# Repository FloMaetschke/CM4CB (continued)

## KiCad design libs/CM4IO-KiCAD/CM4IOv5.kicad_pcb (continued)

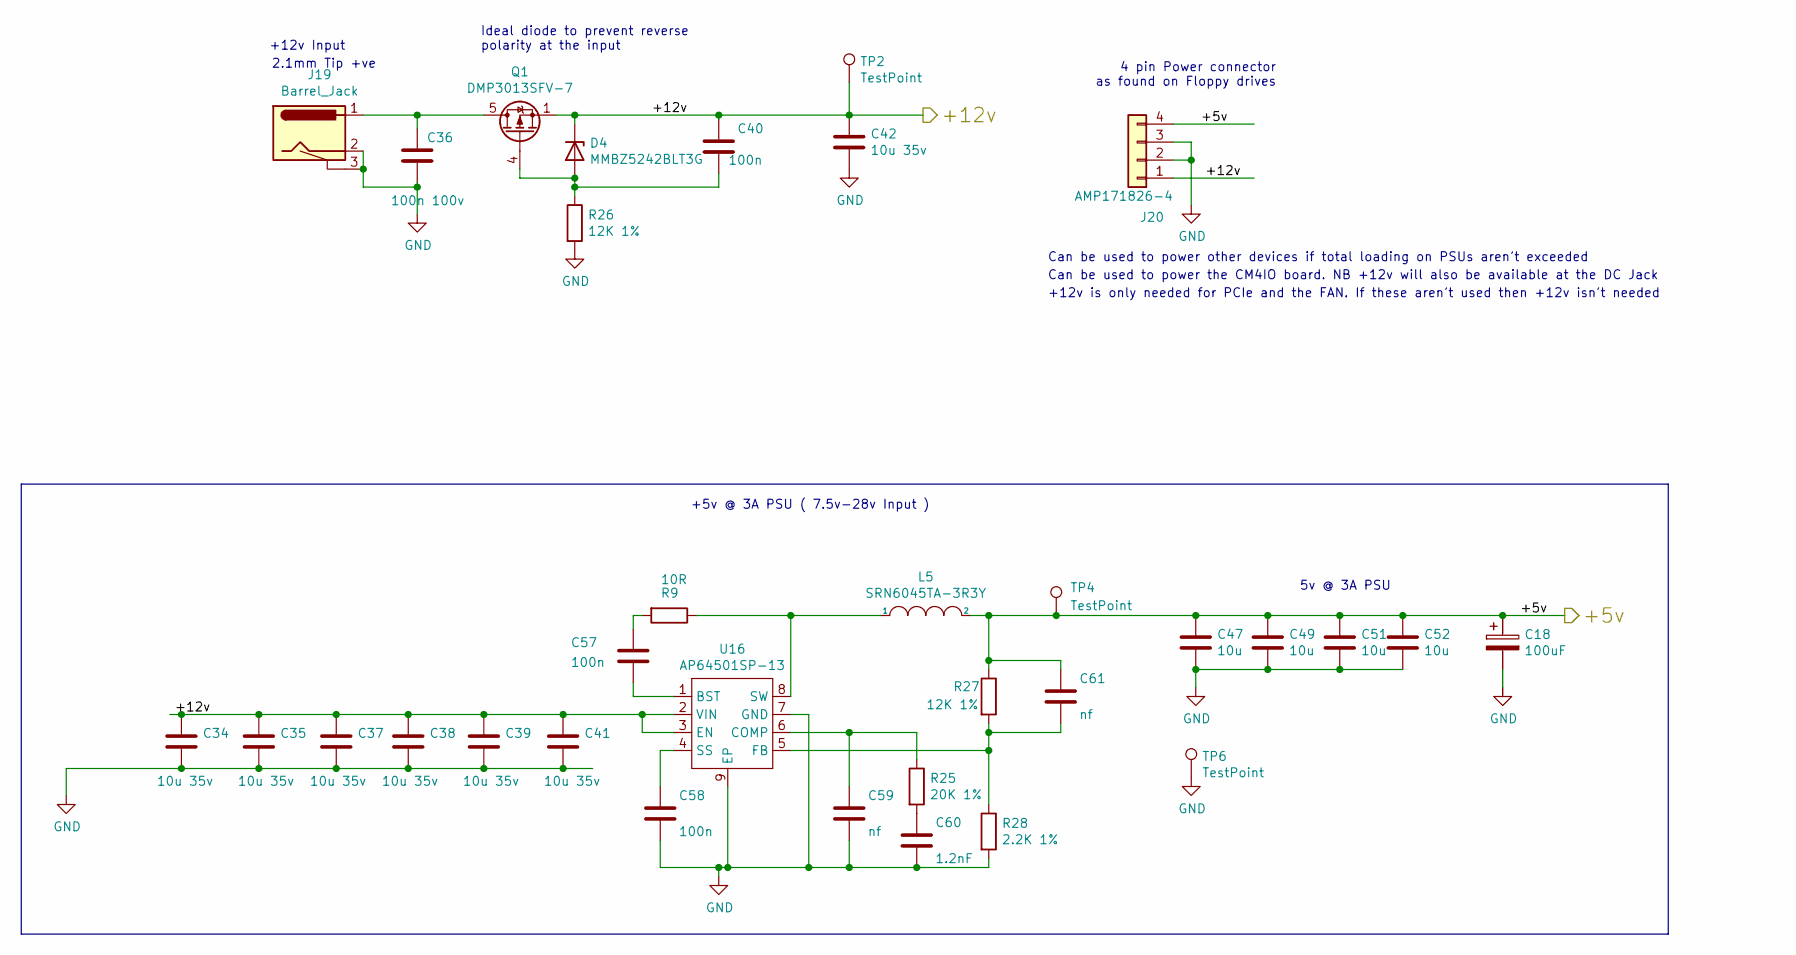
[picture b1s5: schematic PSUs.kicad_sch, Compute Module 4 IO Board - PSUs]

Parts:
C18: 100uF; CP_EIA-7343-31_Kemet-D; Part Description Capacitor, SP-Cap, 100u, 6.3V, 15mR ESR
C34, C35, C37, C38, C39, C41, C42: 10u 35v; C_0805_2012Metric; Part Description 10uF 10% or 20% 35V Ceramic Capacitor X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
C36: 100n 100v; C_0402_1005Metric; Part Description 0.1uF 10% 100V Ceramic Capacitor X5R 04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
C40, C57, C58: 100n; C_0402_1005Metric; Part Description 0.1uF 10% 16V Ceramic Capacitor X7R 040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
C47, C49, C51, C52: 10u; C_0805_2012Metric; Part Description 10uF 10% 10V Ceramic Capacitor X7R 0805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
C59: nf; C_0402_1005Metric
C60: 1.2nF; C_0402_1005Metric; Part Description 1200pF 10% 10V Ceramic Capacitor X5R 04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
C61: nf; C_0402_1005Metric; Part Description 220 pF, 50 V, 0402 [1005 Metric], ± 5%,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
D4: MMBZ5242BLT3G; D_SOT-23_ANK; Part Description Zener Diode 12V 225mW 5% Surface Mount 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
J19: Barrel_Jack; BarrelJack_Horizontal; Part Description DC Power Connectors PCB 2.1MM
J20: AMP171826-4; TE_171826-4; Part Description Wire-To-Board Connector, Right Angle, 2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
L5: SRN6045TA-3R3Y; L_Bourns_SRN6045TA; Part Description 3.3µH Semi-Shielded Wirewound Inductor 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
Q1: DMP3013SFV-7; Diodes_PowerDI3333-8; Part Description DMP3013SFV-7 - Power MOSFET, P Channel,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
R9: 10R; R_0402_1005Metric; Part Description Resistor 10R M1005 1% 63mW
R25: 20K 1%; R_0402_1005Metric; Part Description Resistor 20K M1005 1% 63mW
R26, R27: 12K 1%; R_0402_1005Metric; Part Description Resistor 12K M1005 1% 63mW
R28: 2.2K 1%; R_0402_1005Metric; Part Description Resistor 2.2K M1005 1% 63mW
TP2, TP4, TP6: TestPoint; TestPoint_Pad_2.0x2.0mm
U16: AP64501SP-13; SOIC-8-1EP_3.9x4.9mm_P1.27mm_EP2.95x4.9mm_Mask2.71x3.4mm_Th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; Part Description Buck Switching Regulator IC Positive Ad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

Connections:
/+5v: C18.1, C47.1, C49.1, C51.1, C52.1, C61.1, J20.4, L5.2, R27.1, TP4.1; also elsewhere on the board
/+12v: C34.1, C35.1, C37.1, C38.1, C39.1, C40.1, C41.1, C42.1, D4.1 (K), J20.1, Q1.1 (S), Q1.2 (S), Q1.3 (S), TP2.1, U16.2 (VIN), U16.3 (EN); also elsewhere on the board
GND: C18.2, C34.2, C35.2, C36.2, C37.2, C38.2, C39.2, C41.2, C42.2, C47.2, C49.2, C51.2, C52.2, C58.2, C59.2, C60.2, J19.2, J19.3, J20.2, J20.3, R26.2, R28.2, TP6.1, U16.7 (GND), U16.9 (EP); also elsewhere on the board
unnamed: C36.1, J19.1, Q1.5 (D)
unnamed: C40.2, D4.2 (A), Q1.4 (G), R26.1
unnamed: C57.1, R9.2
unnamed: C57.2, U16.1 (BST)
unnamed: C58.1, U16.4 (SS)
unnamed: C59.1, R25.1, U16.6 (COMP)
unnamed: C60.1, R25.2
unnamed: C61.2, R27.2, R28.1, U16.5 (FB)
unnamed: L5.1, R9.1, U16.8 (SW)

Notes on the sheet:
+12v Input
2.1mm Tip +ve
Ideal diode to prevent reverse polarity at the input
+5v @ 3A PSU ( 7.5v-28v Input )
Can be used to power other devices if total loading on PSUs aren't exceeded
Can be used to power the CM4IO board. NB +12v will also be available at the DC Jack
+12v is only needed for PCIe and the FAN. If these aren't used then +12v isn't needed
4 pin Power connector as found on Floppy drives
5v @ 3A PSU

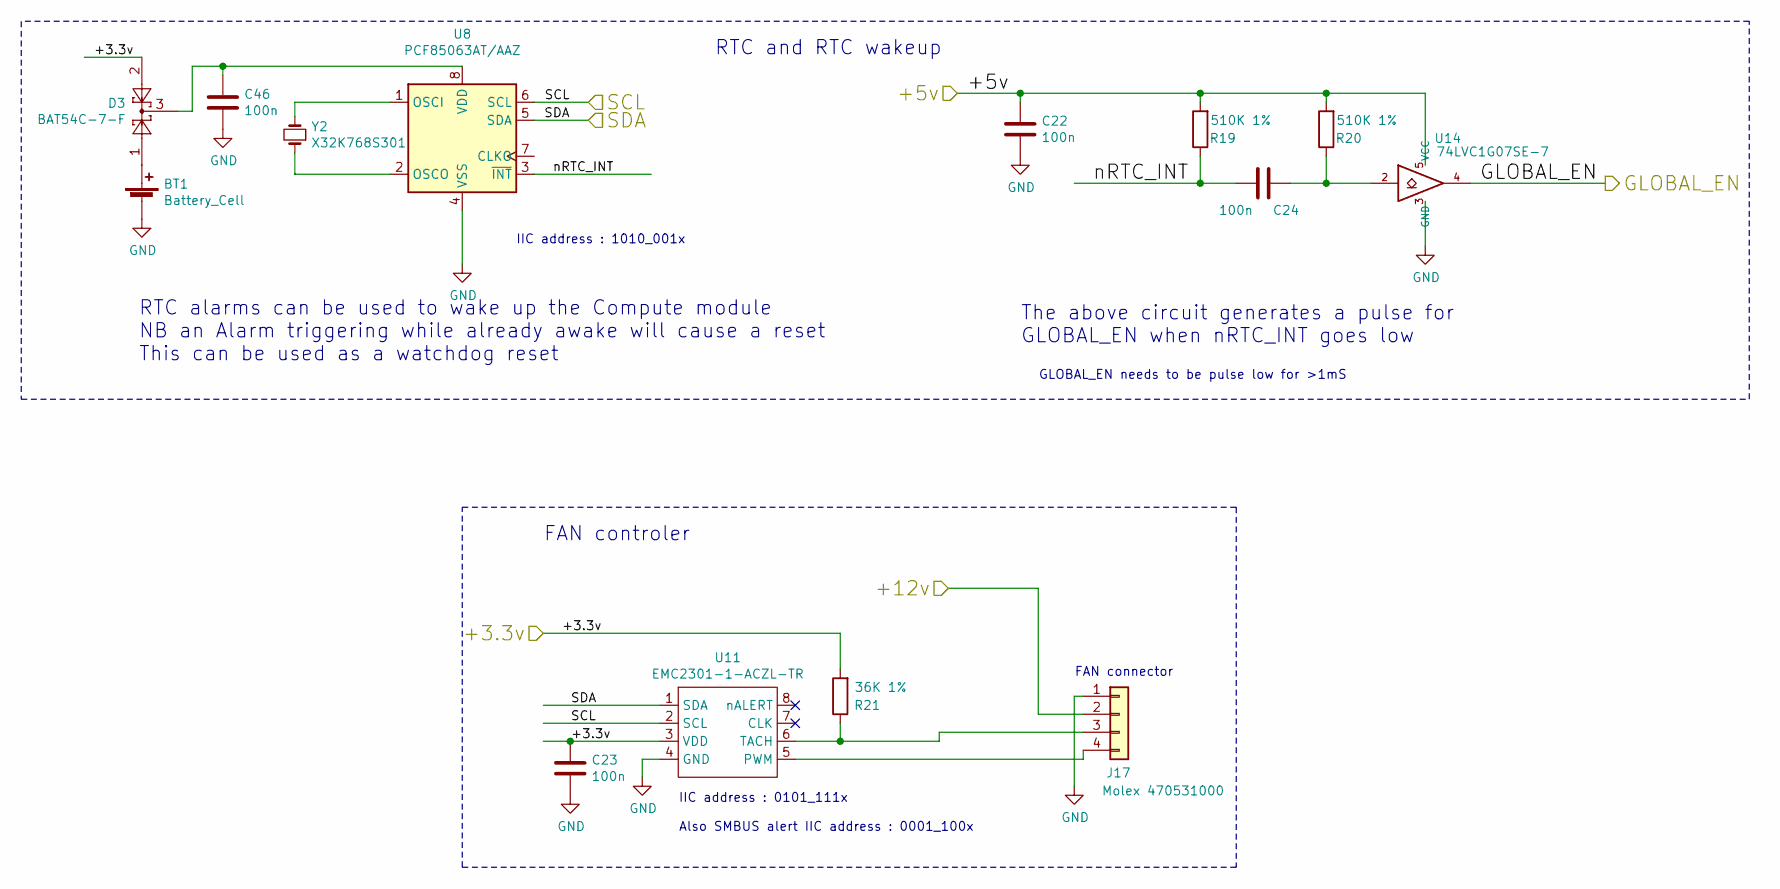
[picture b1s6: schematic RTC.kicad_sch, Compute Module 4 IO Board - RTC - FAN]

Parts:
BT1: Battery_Cell; BatteryHolder_Keystone_3034_1x20mm; Part Description Battery Retainer Coin, 20.0mm 1 Cell SM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
C22, C23, C24, C46: 100n; C_0402_1005Metric; Part Description 0.1uF 10% 16V Ceramic Capacitor X7R 040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
D3: BAT54C-7-F; SOT-23; Part Description Diode Array 1 Pair Common Cathode Schot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
J17: Molex 470531000; FanPinHeader_1x04_P2.54mm_Vertical; Part Description Connector Header Through Hole 4 positio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
R19, R20: 510K 1%; R_0402_1005Metric; Part Description Resistor 510K M1005 1% 63mW
R21: 36K 1%; R_0402_1005Metric; Part Description Resistor 36K M1005 1% 63mW
U8: PCF85063AT/AAZ; SOIC-8_3.9x4.9mm_P1.27mm; Part Description Real Time Clock (RTC) IC Clock/Calendar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
U11: EMC2301-1-ACZL-TR; SOIC-8_5.23x5.23mm_P1.27mm; Part Description Motor Driver PWM 8-MSOP
U14: 74LVC1G07SE-7; SOT-353_SC-70-5; Part Description Buffer, Non-Inverting 1 Element 1 Bit p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
Y2: X32K768S301; Crystal_SMD_3215-2Pin_3.2x1.5mm; Part Description Crystal 32.768KHz 7pF 20pmm

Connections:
/+3.3v: C23.1, D3.2, R21.2, U11.3 (VDD); also elsewhere on the board
/+5v: C22.1, R19.2, R20.2, U14.5 (VCC); also elsewhere on the board
/+12v: J17.2; also elsewhere on the board
/GLOBAL_EN: U14.4; also elsewhere on the board
/RTC , Wakeup, FAN/nRTC_INT: C24.2, R19.1, U8.3 (~INT~)
/SCL0: U8.6 (SCL), U11.2 (SCL); also elsewhere on the board
/SDA0: U8.5 (SDA), U11.1 (SDA); also elsewhere on the board
GND: BT1.2 (-), C22.2, C23.2, C46.2, J17.1, U8.4 (VSS), U11.4 (GND), U14.3 (GND); also elsewhere on the board
unnamed: BT1.1 (+), D3.1
unnamed: C24.1, R20.1, U14.2
unnamed: C46.1, D3.3, U8.8 (VDD)
unnamed: J17.3, R21.1, U11.6 (TACH)
unnamed: J17.4, U11.5 (PWM)
unnamed: U8.1 (OSCI), Y2.2
unnamed: U8.2 (OSCO), Y2.1

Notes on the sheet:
RTC alarms can be used to wake up the Compute module NB an Alarm triggering while already awake will cause a reset This can be used as a watchdog reset
IIC address : 1010_001x
FAN controler
IIC address : 0101_111x
Also SMBUS alert IIC address : 0001_100x
RTC and RTC wakeup
The above circuit generates a pulse for GLOBAL_EN when nRTC_INT goes low
GLOBAL_EN needs to be pulse low for >1mS
FAN connector

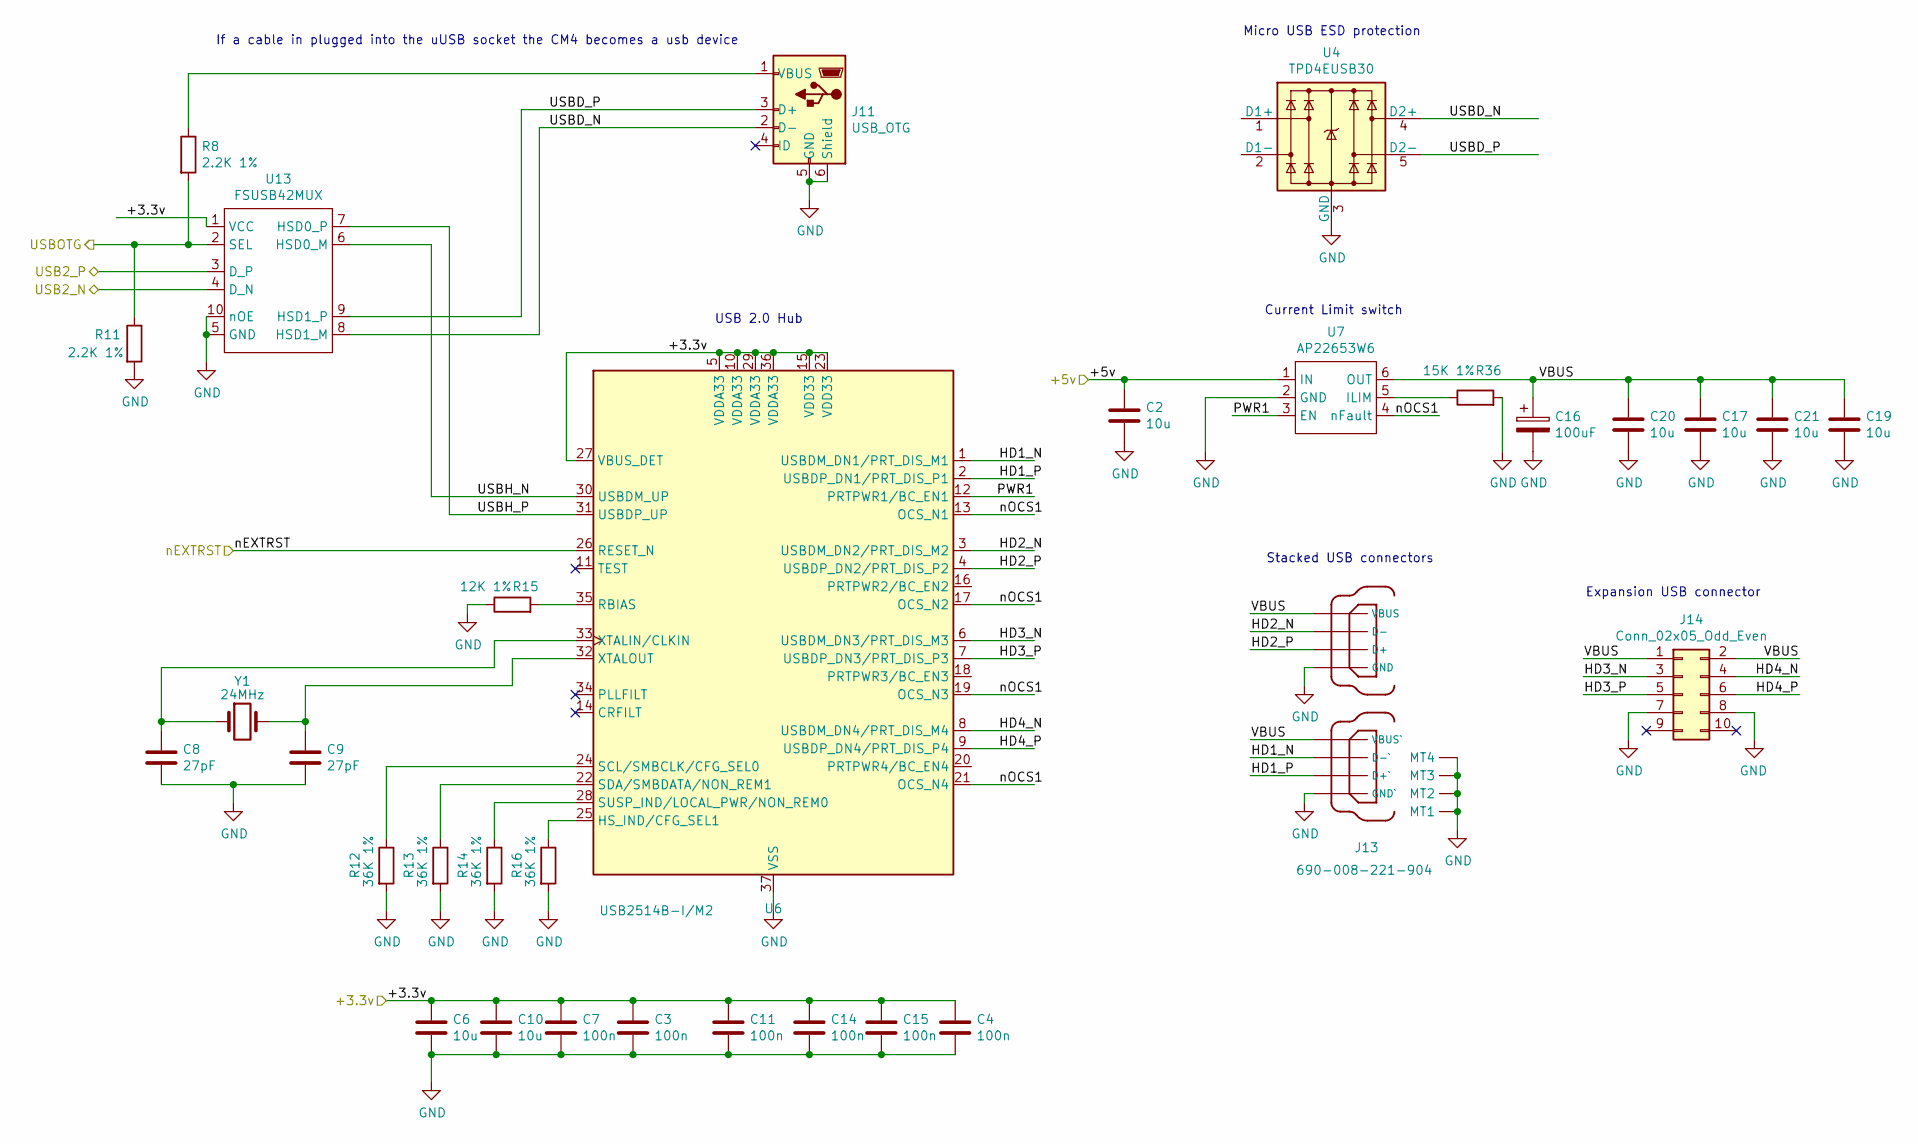
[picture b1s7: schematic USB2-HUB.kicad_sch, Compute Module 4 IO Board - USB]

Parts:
C2, C6, C10, C17, C19, C20, C21: 10u; C_0805_2012Metric; Part Description 10uF 10% 10V Ceramic Capacitor X7R 0805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
C3, C4, C7, C11, C14, C15: 100n; C_0402_1005Metric; Part Description 0.1uF 10% 16V Ceramic Capacitor X7R 040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
C8, C9: 27pF; C_0402_1005Metric; Part Description 27pF 5% 50V Ceramic Capacitor C0G, NP0 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
C16: 100uF; CP_EIA-7343-31_Kemet-D; Part Description Capacitor, SP-Cap, 100u, 6.3V, 15mR ESR
J11: USB_OTG; USB_Micro-B_EDAC_UCON00686; Part Description USB - micro B USB 2.0 Receptacle Connec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
J13: 690-008-221-904; MOLEX_USB_67298-4090; Part Description USB-A (USB TYPE-A), Stacked Receptacle 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
J14: Conn_02x05_Odd_Even; PinHeader_2x05_P2.54mm_Vertical; Part Description PinHeader_2x05_P2.54mm_Vertical
R8, R11: 2.2K 1%; R_0402_1005Metric; Part Description Resistor 2.2K M1005 1% 63mW
R12, R13, R14, R16: 36K 1%; R_0402_1005Metric; Part Description Resistor 36K M1005 1% 63mW
R15: 12K 1%; R_0402_1005Metric; Part Description Resistor 12K M1005 1% 63mW
R36: 15K 1%; R_0402_1005Metric; Part Description Resistor 15K M1005 1% 63mW
U4: TPD4EUSB30; USON-10_2.5x1.0mm_P0.5mm; Part Description Quad TVS diode for high speed signals (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
U6: USB2514B-I/M2; QFN-36-1EP_6x6mm_P0.5mm_EP3.7x3.7mm; Part Description USB Hub Controller USB Interface 36-SQF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
U7: AP22653W6; SOT-23-6; Part Description Power Switch/Driver 1:1 P-Channel 2.1A 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
U13: FSUSB42MUX; MSOP-10_3x3mm_P0.5mm; Part Description USB Switch IC 1 Channel 10-MSOP
Y1: 24MHz; Crystal_SMD_HC49-SD; Part Description 24MHz Crystal 18pf 30ppm 30ppm

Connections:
/+3.3v: C3.1, C4.1, C6.1, C7.1, C10.1, C11.1, C14.1, C15.1, U6.5 (VDDA33), U6.10 (VDDA33), U6.15 (VDD33), U6.23 (VDD33), U6.27 (VBUS_DET), U6.29 (VDDA33), U6.36 (VDDA33), U13.1 (VCC); also elsewhere on the board
/+5v: C2.1, U7.1 (IN); also elsewhere on the board
/USB2-HUB/HD1_N: J13.2 (D-`), U6.1 (USBDM_DN1/PRT_DIS_M1)
/USB2-HUB/HD1_P: J13.3 (D+`), U6.2 (USBDP_DN1/PRT_DIS_P1)
/USB2-HUB/HD2_N: J13.6 (D-), U6.3 (USBDM_DN2/PRT_DIS_M2)
/USB2-HUB/HD2_P: J13.7 (D+), U6.4 (USBDP_DN2/PRT_DIS_P2)
/USB2-HUB/HD3_N: J14.3, U6.6 (USBDM_DN3/PRT_DIS_M3)
/USB2-HUB/HD3_P: J14.5, U6.7 (USBDP_DN3/PRT_DIS_P3)
/USB2-HUB/HD4_N: J14.4, U6.8 (USBDM_DN4/PRT_DIS_M4)
/USB2-HUB/HD4_P: J14.6, U6.9 (USBDP_DN4/PRT_DIS_P4)
/USB2-HUB/PWR1: U6.12 (PRTPWR1/BC_EN1), U7.3 (EN)
/USB2-HUB/USBD_N: J11.2 (D-), U4.4 (D2+), U4.7, U13.8 (HSD1_M)
/USB2-HUB/USBD_P: J11.3 (D+), U4.5 (D2-), U4.6, U13.9 (HSD1_P)
/USB2-HUB/USBH_N: U6.30 (USBDM_UP), U13.6 (HSD0_M)
/USB2-HUB/USBH_P: U6.31 (USBDP_UP), U13.7 (HSD0_P)
/USB2-HUB/VBUS: C16.1, C17.1, C19.1, C20.1, C21.1, J13.1 (VBUS`), J13.5 (VBUS), J14.1, J14.2, U7.6 (OUT)
/USB2-HUB/nOCS1: U6.13 (OCS_N1), U6.17 (OCS_N2), U6.19 (OCS_N3), U6.21 (OCS_N4), U7.4 (nFault)
/USB2_N: U13.4 (D_N); also elsewhere on the board
/USB2_P: U13.3 (D_P); also elsewhere on the board
/USBOTG: R8.2, R11.1, U13.2 (SEL); also elsewhere on the board
/nEXTRST: U6.26 (RESET_N); also elsewhere on the board
GND: C2.2, C3.2, C4.2, C6.2, C7.2, C8.2, C9.2, C10.2, C11.2, C14.2, C15.2, C16.2, C17.2, C19.2, C20.2, C21.2, J11.5 (GND), J11.6 (Shield), J13.4 (GND`), J13.8 (GND), J13.MT1, J13.MT2, J13.MT3, J13.MT4, J14.7, J14.8, R11.2, R12.2, R13.2, R14.2, R15.1, R16.2, R36.2, U4.3 (GND), U4.8 (GND), U6.37 (VSS), U7.2 (GND), U13.5 (GND), U13.10 (nOE); also elsewhere on the board
unnamed: C8.1, U6.33 (XTALIN/CLKIN), Y1.1
unnamed: C9.1, U6.32 (XTALOUT), Y1.2
unnamed: J11.1 (VBUS), R8.1
unnamed: R12.1, U6.24 (SCL/SMBCLK/CFG_SEL0)
unnamed: R13.1, U6.22 (SDA/SMBDATA/NON_REM1)
unnamed: R14.1, U6.28 (SUSP_IND/LOCAL_PWR/NON_REM0)
unnamed: R15.2, U6.35 (RBIAS)
unnamed: R16.1, U6.25 (HS_IND/CFG_SEL1)
unnamed: R36.1, U7.5 (ILIM)
unnamed: U4.1 (D1+), U4.10
unnamed: U4.2 (D1-), U4.9

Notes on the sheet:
If a cable in plugged into the uUSB socket the CM4 becomes a usb device
USB 2.0 Hub
Current Limit switch
Micro USB ESD protection
Stacked USB connectors
Expansion USB connector

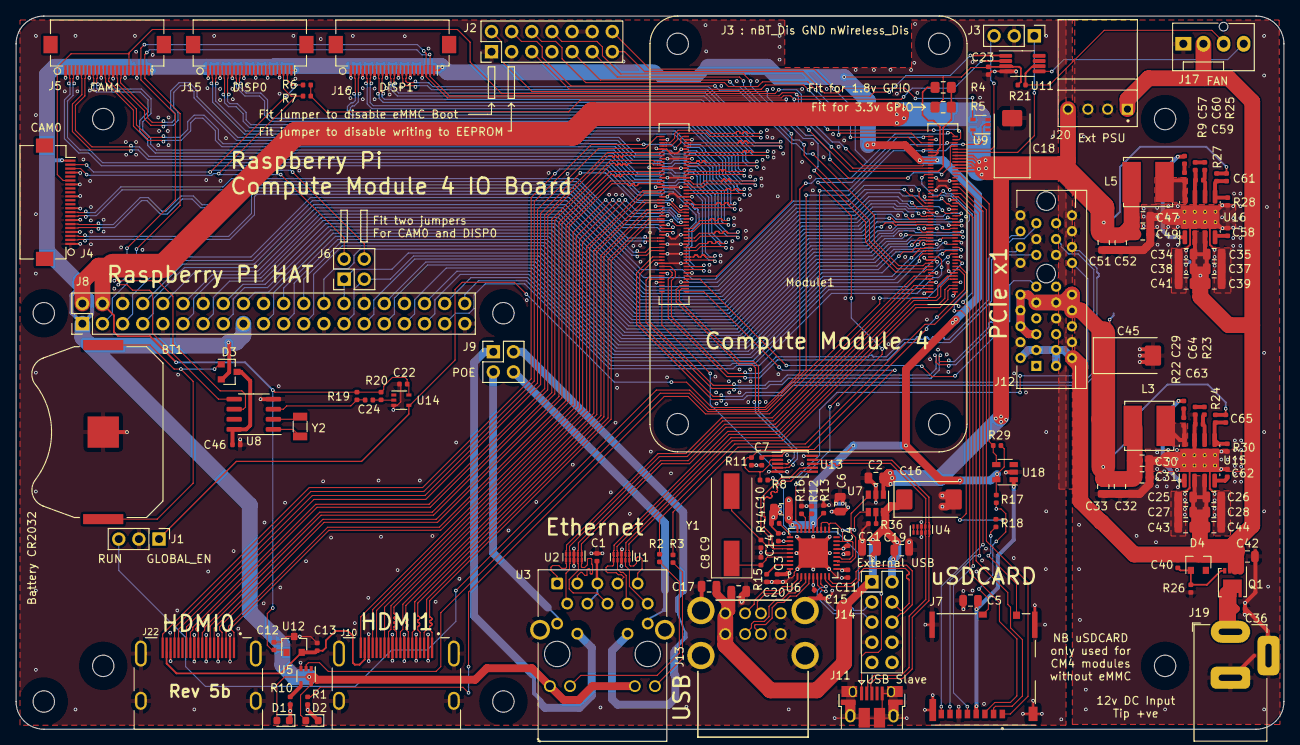
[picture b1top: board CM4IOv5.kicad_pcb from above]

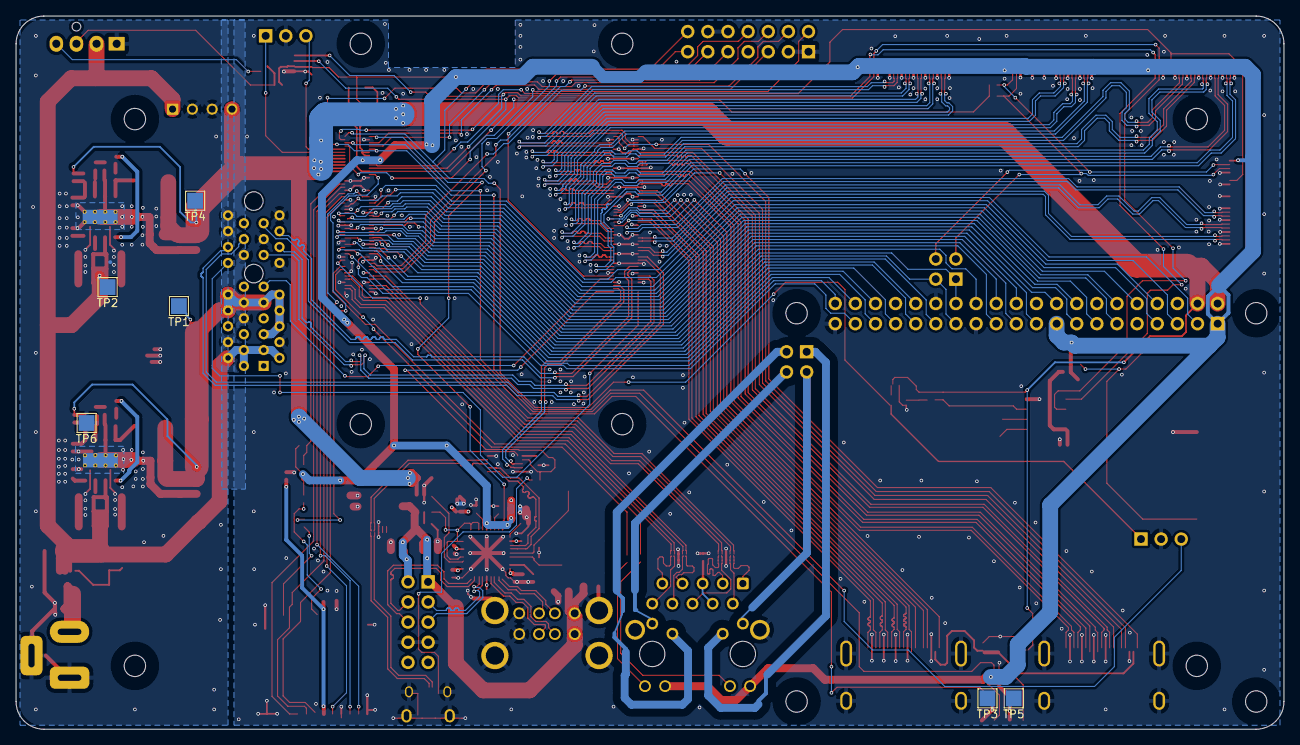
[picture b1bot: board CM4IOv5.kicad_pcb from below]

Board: 4 copper layers, 160.0 x 90.0 mm, 151 parts (6 on the bottom side), 204 nets.

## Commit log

2020-10-26 project setup
2020-10-28 recreate repo without datasheets
2020-11-02 updated schematics
2020-11-02 readme updated
